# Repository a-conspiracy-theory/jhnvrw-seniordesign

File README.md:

UCF 2026 Senior Design Project

RF Energy Harvesting Ultra-Low-power Transceiver for Environmental Sensing

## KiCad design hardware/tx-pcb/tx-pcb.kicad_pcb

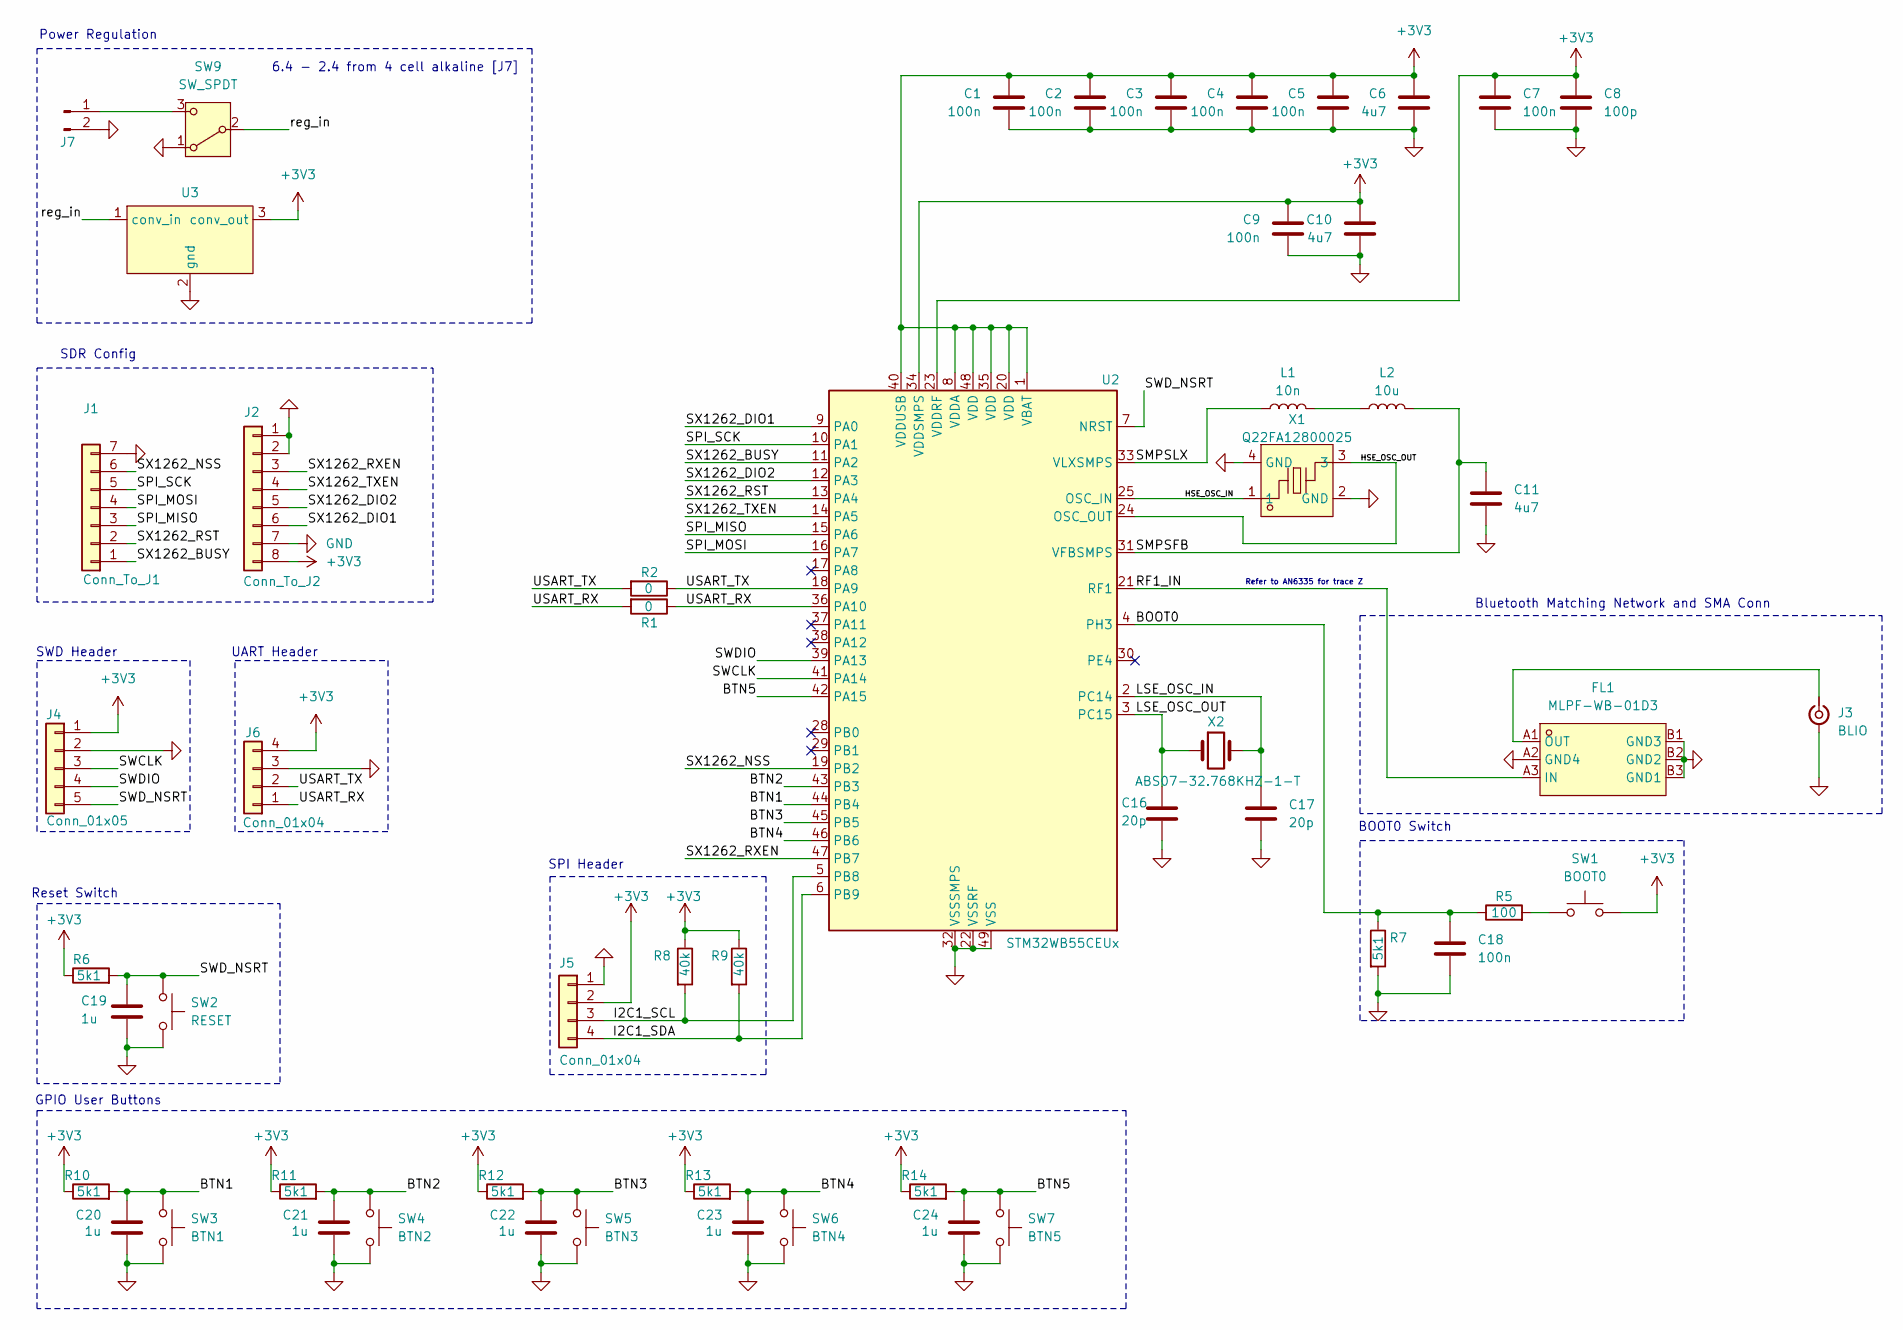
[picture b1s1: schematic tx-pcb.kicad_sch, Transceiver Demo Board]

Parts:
C1, C2, C3, C4, C5, C7, C9, C18: 100n; C_0603_1608Metric_Pad1.08x0.95mm_HandSolder
C6, C10, C11: 4u7; C_0603_1608Metric_Pad1.08x0.95mm_HandSolder
C8: 100p; C_0603_1608Metric_Pad1.08x0.95mm_HandSolder
C16, C17: 20p; C_0603_1608Metric_Pad1.08x0.95mm_HandSolder
C19, C20, C21, C22, C23, C24: 1u; C_0603_1608Metric_Pad1.08x0.95mm_HandSolder
FL1: MLPF-WB-01D3; BGA-6_L1.6-W1.0-R3-C2-P0.50-TL; MPN MLPF-WB-01D3; LCSC Part C5440144
J1: Conn_To_J1; PinHeader_1x07_P2.54mm_Vertical
J2: Conn_To_J2; PinHeader_1x08_P2.54mm_Vertical
J3: BLIO; SMA_Samtec_SMA-J-P-H-ST-EM1_EdgeMount
J4: Conn_01x05; PinHeader_1x05_P2.54mm_Vertical
J5, J6: Conn_01x04; PinHeader_1x04_P2.54mm_Vertical
J7: Conn_01x02_Pin; PinHeader_1x02_P2.54mm_Vertical
L1: 10n; L_0805_2012Metric_Pad1.05x1.20mm_HandSolder
L2: 10u; L_0805_2012Metric_Pad1.05x1.20mm_HandSolder
R1, R2: 0; R_0805_2012Metric_Pad1.20x1.40mm_HandSolder
R5: 100; R_0805_2012Metric_Pad1.20x1.40mm_HandSolder
R6, R7, R10, R11, R12, R13, R14: 5k1; R_0805_2012Metric_Pad1.20x1.40mm_HandSolder
R8, R9: 40k; R_0805_2012Metric_Pad1.20x1.40mm_HandSolder
SW1: BOOT0; SW_PUSH_6mm
SW2: RESET; SW_PUSH_6mm
SW3: BTN1; SW_PUSH_6mm
SW4: BTN2; SW_PUSH_6mm
SW5: BTN3; SW_PUSH_6mm
SW6: BTN4; SW_PUSH_6mm
SW7: BTN5; SW_PUSH_6mm
SW9: SW_SPDT; spdt_amazon
U2: STM32WB55CEUx; QFN-48-1EP_7x7mm_P0.5mm_EP5.6x5.6mm
U3: TPS63070_board
X1: Q22FA12800025; CRYSTAL-SMD_4P-L2.0-W1.6-BL; MPN Q22FA12800025; LCSC Part C187794
X2: ABS07-32.768KHZ-1-T; OSC-SMD_2P-L3.2-W1.5

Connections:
+3V3: C1.1, C2.1, C3.1, C4.1, C5.1, C6.1, C7.1, C8.1, C9.1, C10.1, J2.8, J4.1, J5.2, J6.4, R6.1, R8.1, R9.1, R10.1, R11.1, R12.1, R13.1, R14.1, SW1.2, U2.1 (VBAT), U2.8 (VDDA), U2.20 (VDD), U2.23 (VDDRF), U2.34 (VDDSMPS), U2.35 (VDD), U2.40 (VDDUSB), U2.48 (VDD), U3.3 (conv_out)
/BOOT0: C18.2, R5.1, R7.1, U2.4 (PH3)
/BTN1: C20.1, R10.2, SW3.1, U2.44 (PB4)
/BTN2: C21.1, R11.2, SW4.1, U2.43 (PB3)
/BTN3: C22.1, R12.2, SW5.1, U2.45 (PB5)
/BTN4: C23.1, R13.2, SW6.1, U2.46 (PB6)
/BTN5: C24.1, R14.2, SW7.1, U2.42 (PA15)
/HSE_OSC_IN: U2.25 (OSC_IN), X1.1
/HSE_OSC_OUT: U2.24 (OSC_OUT), X1.3
/I2C1_SCL: J5.3, R8.2, U2.5 (PB8)
/I2C1_SDA: J5.4, R9.2, U2.6 (PB9)
/LSE_OSC_IN: C17.1, U2.2 (PC14), X2.2
/LSE_OSC_OUT: C16.1, U2.3 (PC15), X2.1
/RF1_IN: FL1.A3 (IN), U2.21 (RF1)
/SMPSFB: C11.1, L2.2, U2.31 (VFBSMPS)
/SMPSLX: L1.1, U2.33 (VLXSMPS)
/SPI_MISO: J1.3, U2.15 (PA6)
/SPI_MOSI: J1.4, U2.16 (PA7)
/SPI_SCK: J1.5, U2.10 (PA1)
/SWCLK: J4.3, U2.41 (PA14)
/SWDIO: J4.4, U2.39 (PA13)
/SWD_NSRT: C19.1, J4.5, R6.2, SW2.1, U2.7 (NRST)
/SX1262_BUSY: J1.1, U2.11 (PA2)
/SX1262_DIO1: J2.6, U2.9 (PA0)
/SX1262_DIO2: J2.5, U2.12 (PA3)
/SX1262_NSS: J1.6, U2.19 (PB2)
/SX1262_RST: J1.2, U2.13 (PA4)
/SX1262_RXEN: J2.3, U2.47 (PB7)
/SX1262_TXEN: J2.4, U2.14 (PA5)
/USART_RX: J6.1, R1.1, R1.2, U2.36 (PA10)
/USART_TX: J6.2, R2.1, R2.2, U2.18 (PA9)
/reg_in: SW9.2 (B), U3.1 (conv_in)
GND: C1.2, C2.2, C3.2, C4.2, C5.2, C6.2, C7.2, C8.2, C9.2, C10.2, C11.2, C16.2, C17.2, C18.1, C19.2, C20.2, C21.2, C22.2, C23.2, C24.2, FL1.A2 (GND4), FL1.B1 (GND3), FL1.B2 (GND2), FL1.B3 (GND1), J1.7, J2.1, J2.2, J2.7, J3.2 (Ext), J4.2, J5.1, J6.3, J7.2, R7.2, SW2.2, SW3.2, SW4.2, SW5.2, SW6.2, SW7.2, SW9.1 (A), U2.22 (VSSRF), U2.32 (VSSSMPS), U2.49 (VSS), U3.2 (gnd), X1.2 (GND), X1.4 (GND)
unnamed: FL1.A1 (OUT), J3.1 (In)
unnamed: J7.1, SW9.3 (C)
unnamed: L1.2, L2.1
unnamed: R5.2, SW1.1

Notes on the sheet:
Power Regulation
6.4 - 2.4 from 4 cell alkaline [J7]
SPI Header
SWD Header
SDR Config
Reset Switch
GPIO User Buttons
Bluetooth Matching Network and SMA Conn
BOOT0 Switch
Refer to AN6335 for trace Z
UART Header

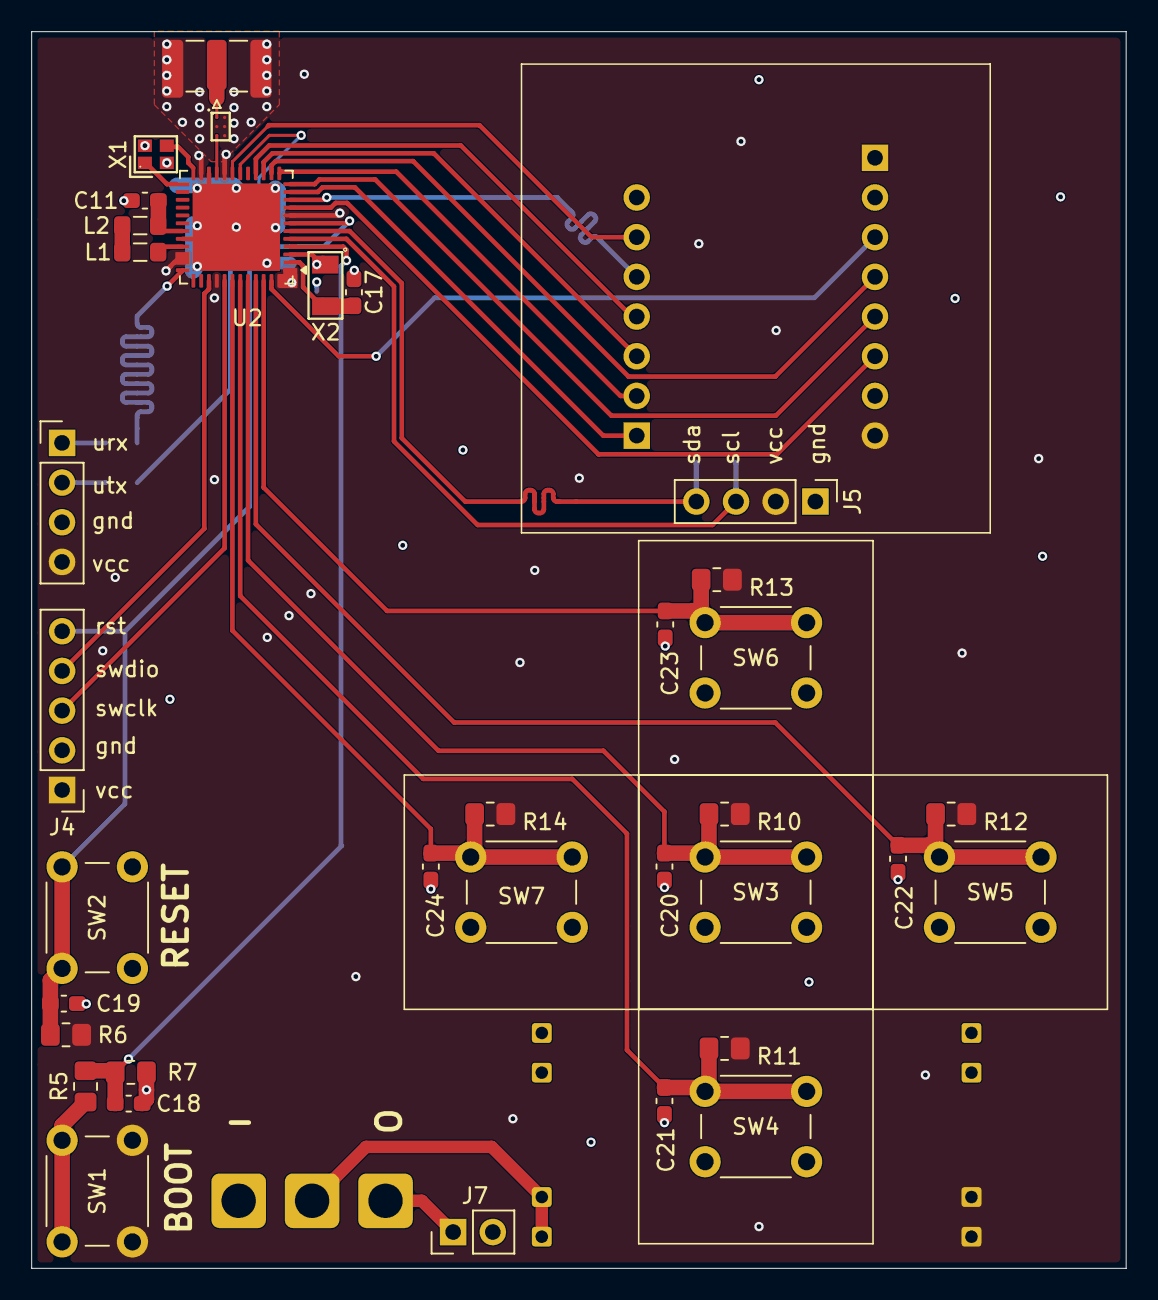
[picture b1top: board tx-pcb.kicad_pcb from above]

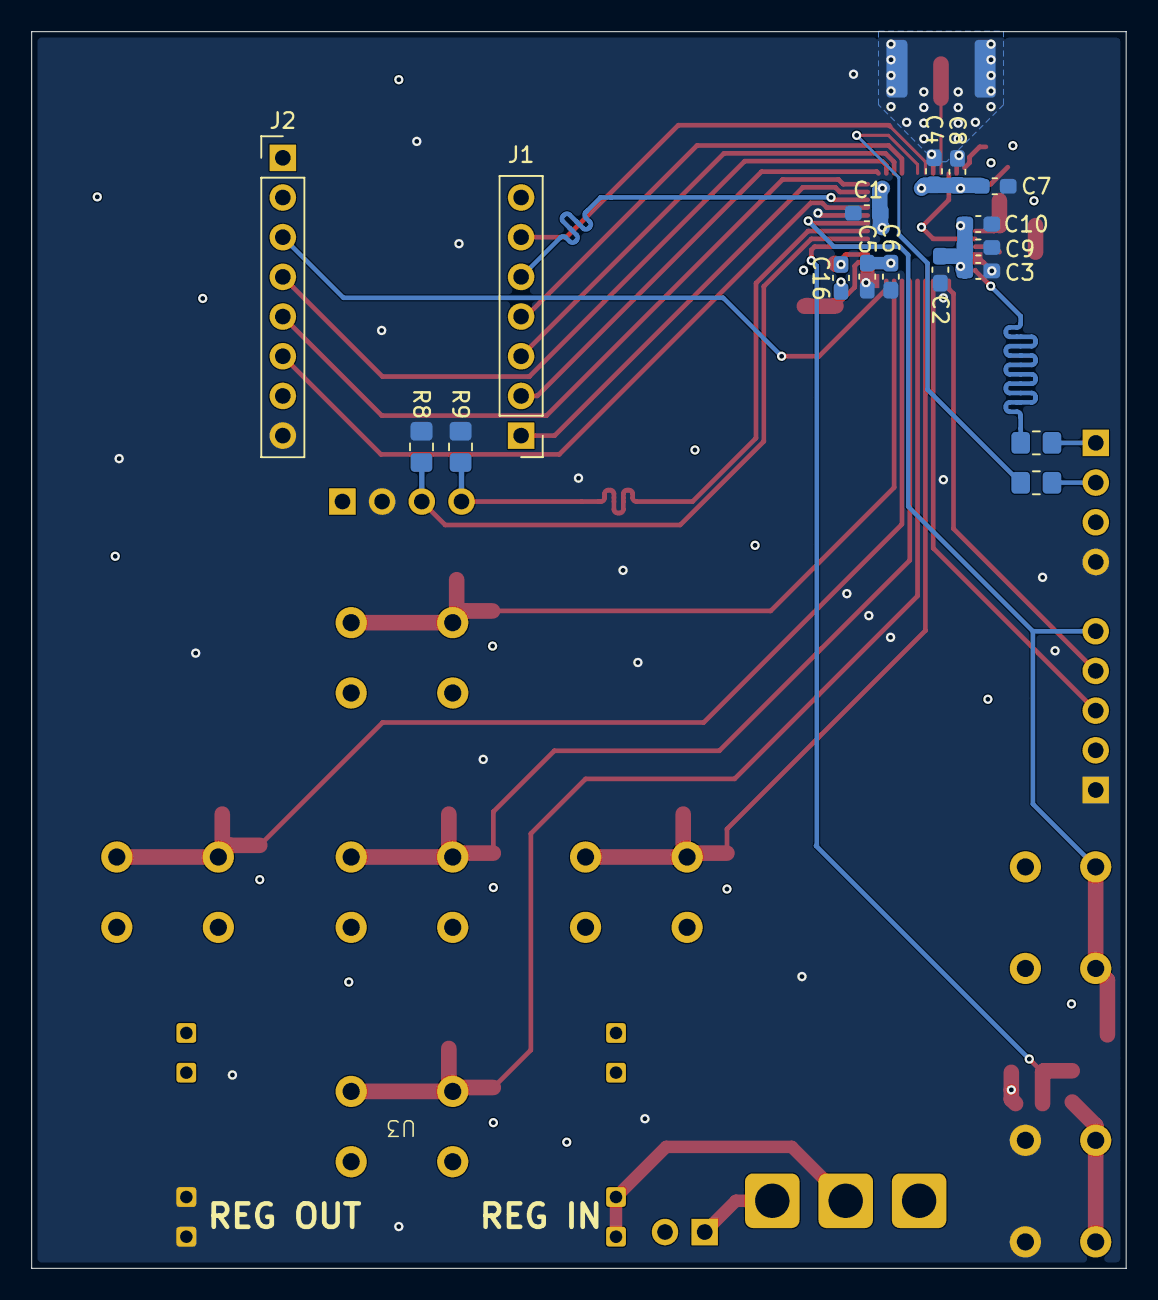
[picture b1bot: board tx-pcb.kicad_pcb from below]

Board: 4 copper layers, 70.0 x 79.1 mm, 54 parts (18 on the bottom side), 37 nets.

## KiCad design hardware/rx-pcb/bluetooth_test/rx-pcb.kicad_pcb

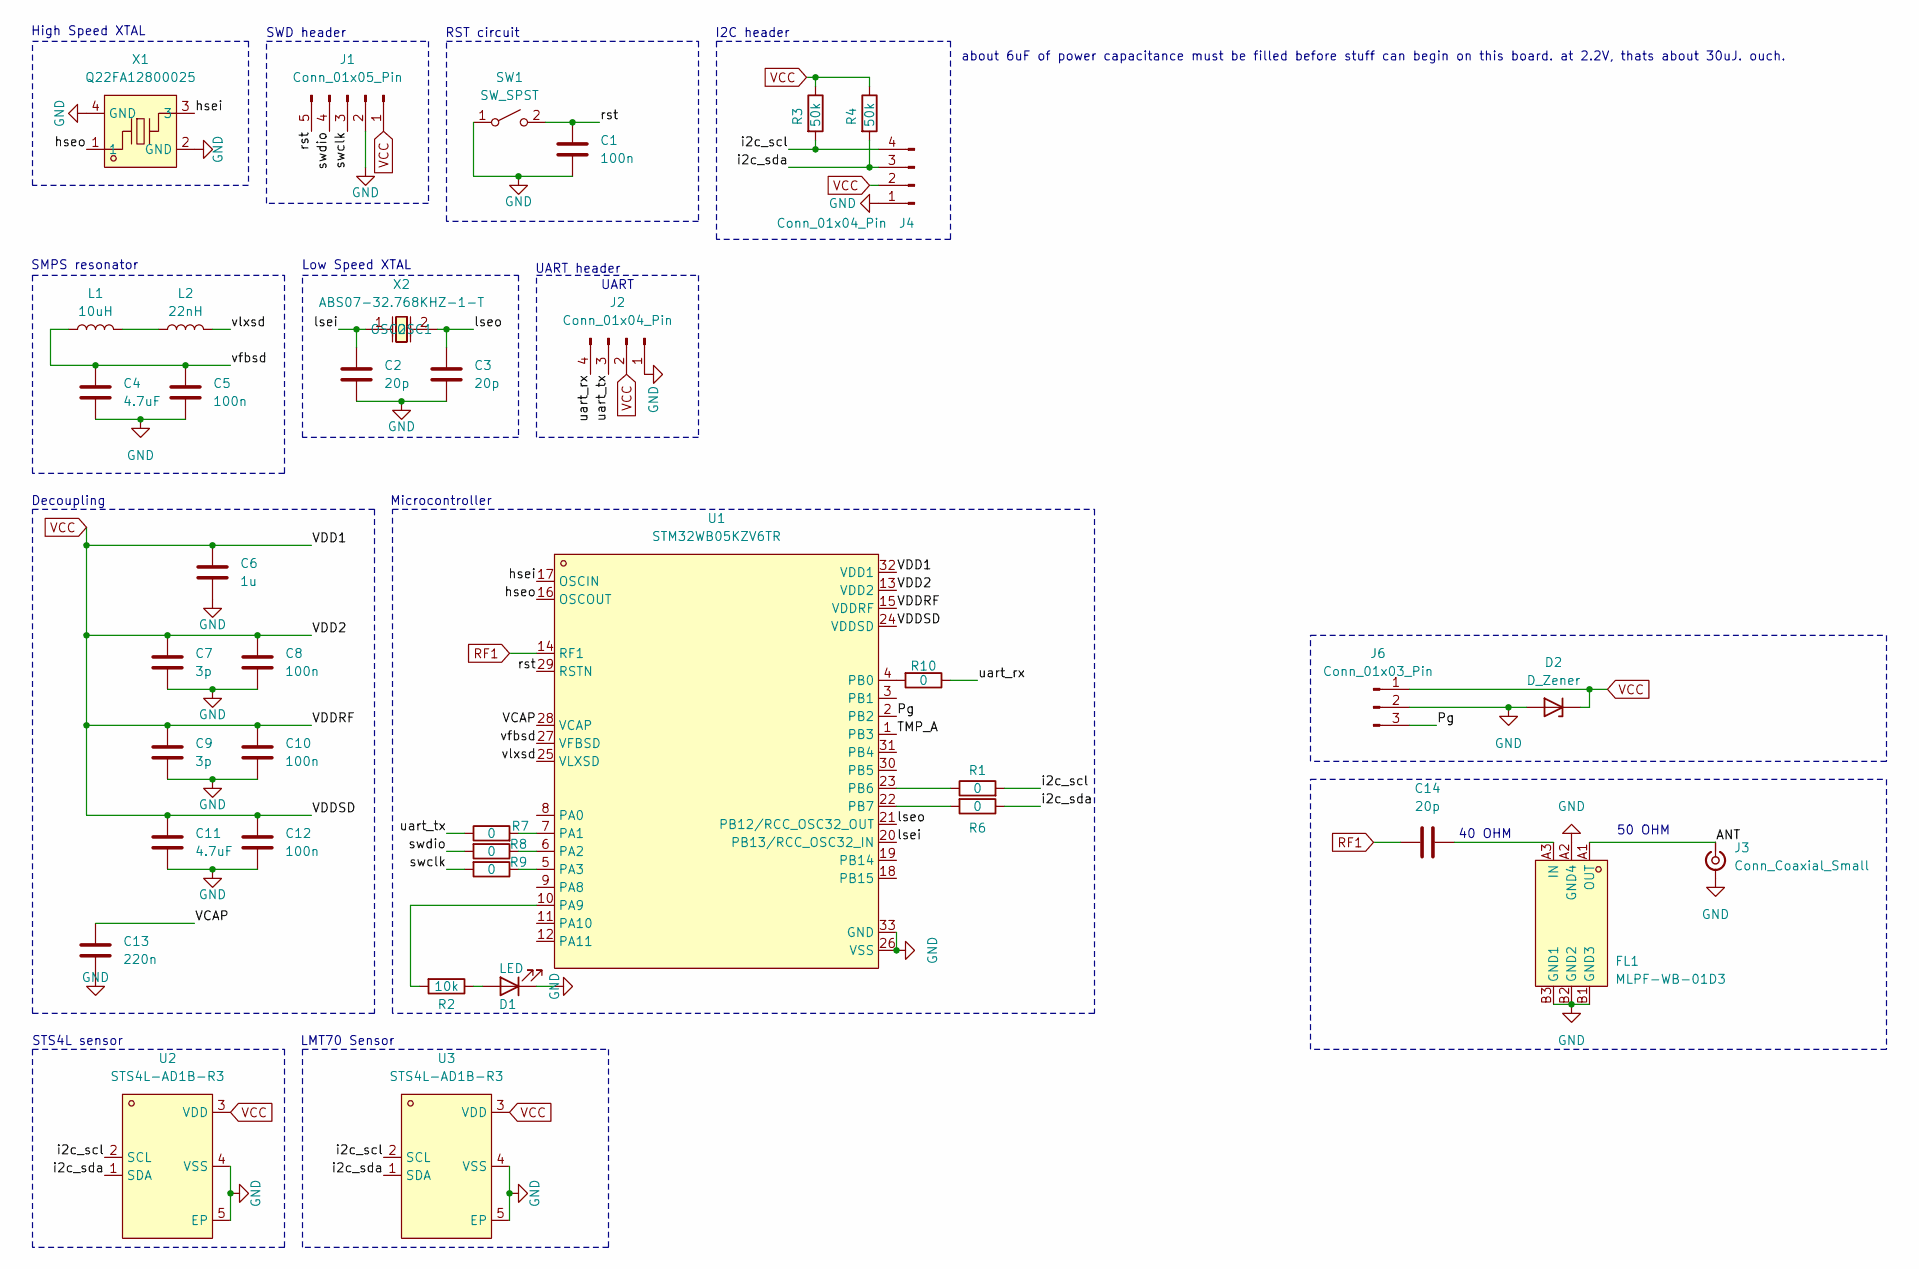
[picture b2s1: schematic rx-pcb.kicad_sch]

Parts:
C1, C5, C8, C10, C12: 100n; C_0805_2012Metric_Pad1.18x1.45mm_HandSolder
C2, C3: 20p; C_0805_2012Metric_Pad1.18x1.45mm_HandSolder
C4, C11: 4.7uF; C_0805_2012Metric_Pad1.18x1.45mm_HandSolder
C6: 1u; C_0805_2012Metric_Pad1.18x1.45mm_HandSolder
C7, C9: 3p; C_0805_2012Metric_Pad1.18x1.45mm_HandSolder
C13: 220n; C_0805_2012Metric_Pad1.18x1.45mm_HandSolder
C14: 20p; R_0201_0603Metric_Pad0.64x0.40mm_HandSolder_correctedcleara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
D1: LED; LED_0805_2012Metric_Pad1.15x1.40mm_HandSolder
D2: D_Zener; D_0603_1608Metric_Pad1.05x0.95mm_HandSolder
FL1: MLPF-WB-01D3; BGA-6_L1.6-W1.0-R3-C2-P0.50-TL; MPN MLPF-WB-01D3; LCSC Part C5440144
J1: Conn_01x05_Pin; PinHeader_1x05_P2.54mm_Vertical
J2, J4: Conn_01x04_Pin; PinHeader_1x04_P2.54mm_Vertical
J3: Conn_Coaxial_Small; SMA_Samtec_SMA-J-P-H-ST-EM1_EdgeMount
J6: Conn_01x03_Pin; PinHeader_1x03_P2.54mm_Vertical
L1: 10uH; L_0805_2012Metric_Pad1.05x1.20mm_HandSolder
L2: 22nH; L_0805_2012Metric_Pad1.05x1.20mm_HandSolder
R1, R6: 0; R_0805_2012Metric_Pad1.20x1.40mm_HandSolder
R2: 10k; R_0805_2012Metric_Pad1.20x1.40mm_HandSolder
R3, R4: 50k; R_0805_2012Metric_Pad1.20x1.40mm_HandSolder
R7, R8, R9, R10: 0; R_0805_2012Metric
SW1: SW_SPST; SW_PUSH_6mm
U1: STM32WB05KZV6TR; UFQFN-32_L5.0-W5.0-P0.50-TL-EP3.5; MPN STM32WB05KZV6TR; LCSC Part C28314403
U2, U3: STS4L-AD1B-R3; DFN-4_L1.5-W1.5-P0.80-TL-EP; MPN STS4L-AD1B-R3; LCSC Part C41410764
X1: Q22FA12800025; CRYSTAL-SMD_4P-L2.0-W1.6-BL; MPN Q22FA12800025; LCSC Part C187794
X2: ABS07-32.768KHZ-1-T; OSC-SMD_2P-L3.2-W1.5; MPN ABS07-32.768KHz-1-T; LCSC Part C145140

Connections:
/ANT: FL1.A1 (OUT), J3.1 (In)
/Pg: J6.3, U1.2 (PB2)
/TMP_A: U1.1 (PB3)
/VCAP: C13.1, U1.28 (VCAP)
/hsei: U1.17 (OSCIN), X1.3
/hseo: U1.16 (OSCOUT), X1.1
/i2c_scl: J4.4, R1.2, R3.2, U2.2 (SCL), U3.2 (SCL)
/i2c_sda: J4.3, R4.2, R6.1, U2.1 (SDA), U3.1 (SDA)
/lsei: C2.1, U1.20 (PB13/RCC_OSC32_IN), X2.1 (OSC1)
/lseo: C3.1, U1.21 (PB12/RCC_OSC32_OUT), X2.2 (OSC2)
/rst: C1.1, J1.5, SW1.2 (B), U1.29 (RSTN)
/swclk: J1.3, R9.2
/swdio: J1.4, R8.2
/uart_rx: J2.4, R10.1
/uart_tx: J2.3, R7.1
/vfbsd: C4.1, C5.1, L1.1, U1.27 (VFBSD)
/vlxsd: L2.2, U1.25 (VLXSD)
GND: C1.2, C2.2, C3.2, C4.2, C5.2, C6.2, C7.2, C8.2, C9.2, C10.2, C11.2, C12.2, C13.2, D1.1 (K), D2.2 (A), FL1.A2 (GND4), FL1.B1 (GND3), FL1.B2 (GND2), FL1.B3 (GND1), J1.2, J2.1, J3.2 (Ext), J4.1, J6.2, SW1.1 (A), U1.26 (VSS), U1.33 (GND), U2.4 (VSS), U2.5 (EP), U3.4 (VSS), U3.5 (EP), X1.2 (GND), X1.4 (GND)
unnamed: D1.2 (A), R2.1
unnamed: C14.2, FL1.A3 (IN)
unnamed: L1.2, L2.1
unnamed: R7.2, U1.7 (PA1)
unnamed: R8.1, U1.6 (PA2)
unnamed: R9.1, U1.5 (PA3)
unnamed: R2.2, U1.10 (PA9)
unnamed: R10.2, U1.4 (PB0)
unnamed: R1.1, U1.23 (PB6)
unnamed: R6.2, U1.22 (PB7)
RF1: C14.1, U1.14 (RF1)
VCC: C6.1, C7.1, C8.1, C9.1, C10.1, C11.1, C12.1, D2.1 (K), J1.1, J2.2, J4.2, J6.1, R3.1, R4.1, U1.13 (VDD2), U1.15 (VDDRF), U1.24 (VDDSD), U1.32 (VDD1), U2.3 (VDD), U3.3 (VDD)

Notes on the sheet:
Low Speed XTAL
about 6uF of power capacitance must be filled before stuff can begin on this board. at 2.2V, thats about 30uJ. ouch.
40 OHM
UART header
LMT70 Sensor
RST circuit
Microcontroller
SWD header
High Speed XTAL
UART
Decoupling
STS4L sensor
I2C header
SMPS resonator
50 OHM

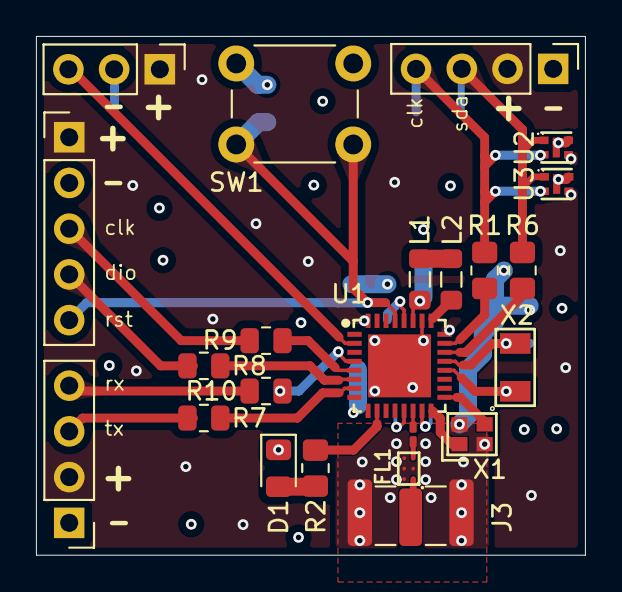
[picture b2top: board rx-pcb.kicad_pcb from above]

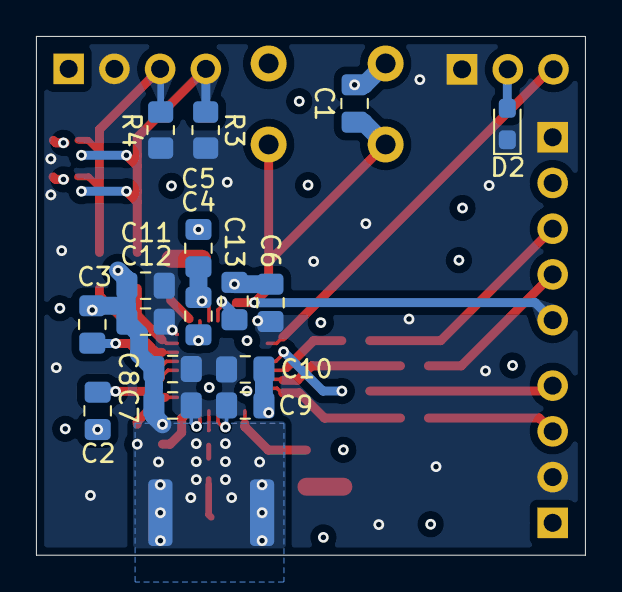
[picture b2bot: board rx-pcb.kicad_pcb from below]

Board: 4 copper layers, 30.5 x 28.8 mm, 39 parts (16 on the bottom side), 29 nets.

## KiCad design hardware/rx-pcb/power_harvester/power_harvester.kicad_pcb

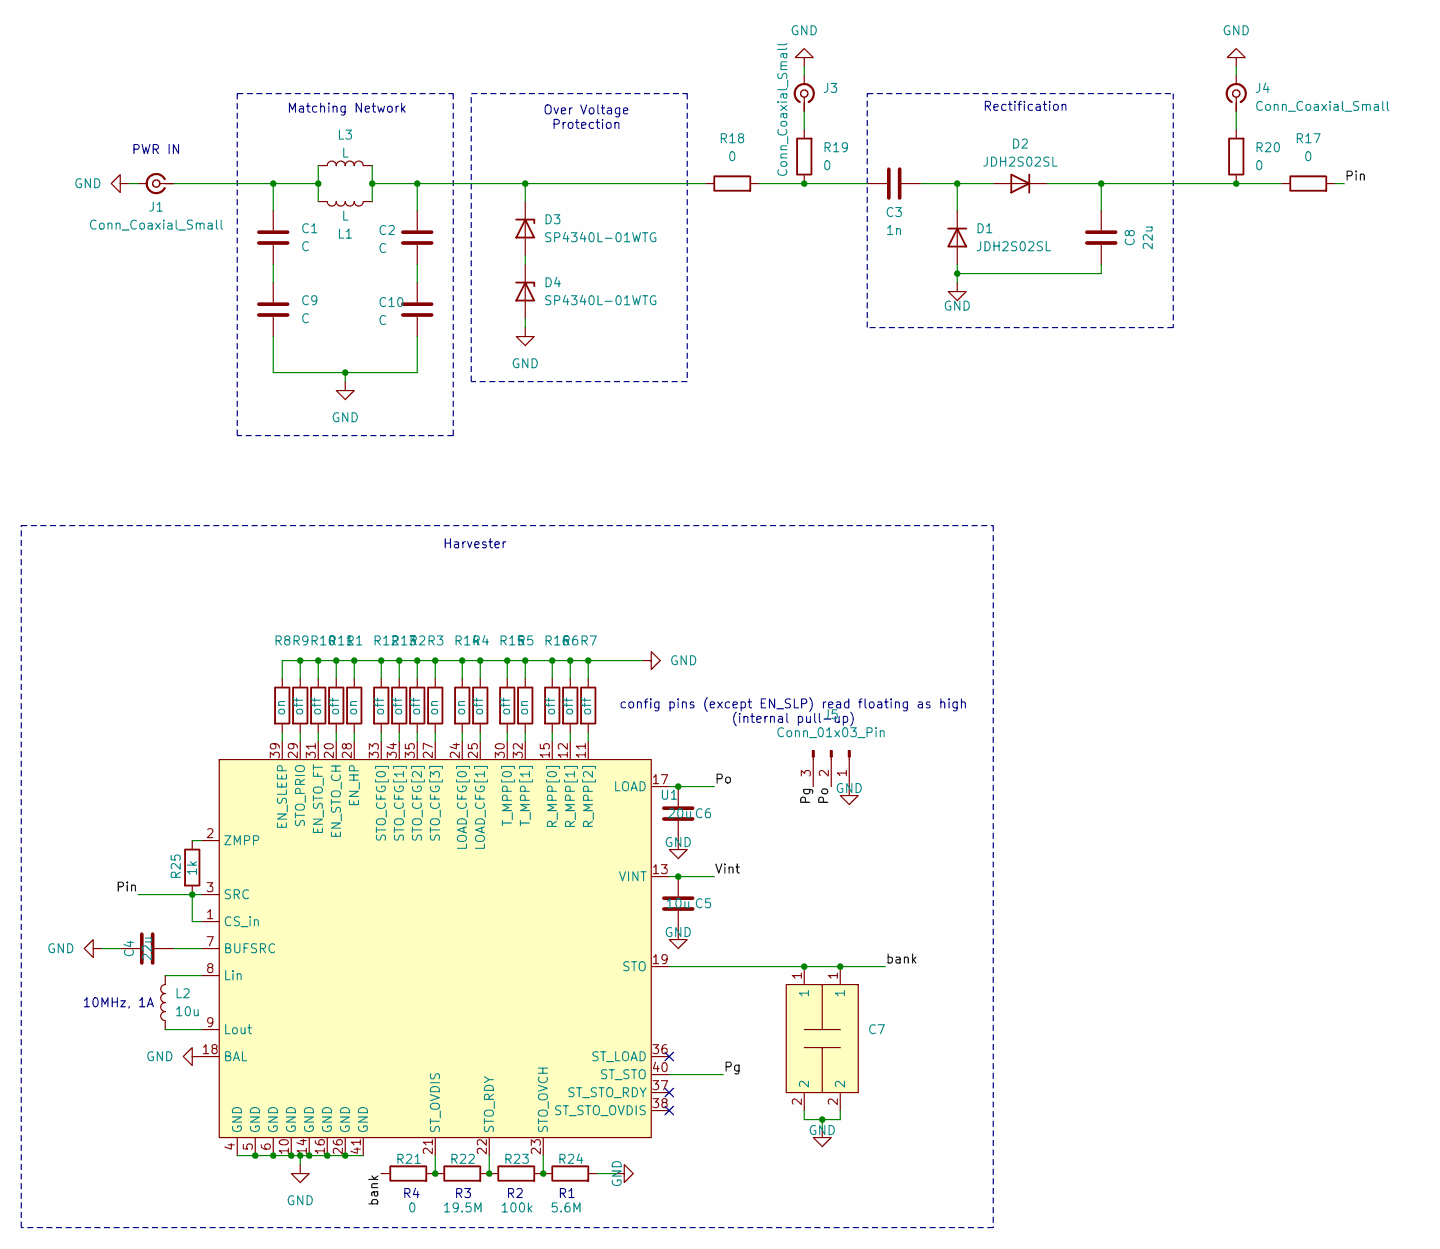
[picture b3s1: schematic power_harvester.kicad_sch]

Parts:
C1, C2, C9, C10: C; C_0402_1005Metric
C3: 1n; C_0402_1005Metric
C4: 22u; C_0603_1608Metric_Pad1.08x0.95mm_HandSolder
C5: 10u; C_0603_1608Metric_Pad1.08x0.95mm_HandSolder
C6: 20u; C_0603_1608Metric_Pad1.08x0.95mm_HandSolder
C7: C4AQXEXXXXXXXAX
C8: 22u; C_0805_2012Metric_Pad1.18x1.45mm_HandSolder
D1, D2: JDH2S02SL; R_0201_0603Metric_correctedclearance
D3, D4: SP4340L-01WTG; R_0201_0603Metric_correctedclearance
J1: Conn_Coaxial_Small; SMA_Amphenol_901-143_Horizontal
J3, J4: Conn_Coaxial_Small; SMA_Molex_73251-2120_EdgeMount_Horizontal
J5: Conn_01x03_Pin; PinHeader_1x03_P2.54mm_Vertical
L1, L3: L; L_0402_1005Metric
L2: 10u; WE-MAPI
R1, R3, R5, R8, R14: on; R_0201_0603Metric_correctedclearance
R2, R4, R6, R7, R9, R10, R11, R12, R13, R15, R16: off; R_0201_0603Metric_correctedclearance
R17, R18, R19, R20: 0; R_0201_0603Metric_correctedclearance
R21: 0; R_0805_2012Metric_Pad1.20x1.40mm_HandSolder
R22: 19.5M; R_0805_2012Metric_Pad1.20x1.40mm_HandSolder
R23: 100k; R_0805_2012Metric_Pad1.20x1.40mm_HandSolder
R24: 5.6M; R_0805_2012Metric_Pad1.20x1.40mm_HandSolder
R25: 1k; R_0805_2012Metric_Pad1.20x1.40mm_HandSolder
U1: QFN-40-1EP_5x5mm_P0.4mm_EP3.8x3.8mm

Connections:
/Pg: J5.3, U1.40 (ST_STO)
/Pin: R17.2, R25.2, U1.1 (CS_in), U1.3 (SRC)
/Po: C6.2, J5.2, U1.17 (LOAD)
/Vint: C5.2, U1.13 (VINT)
/bank: C7.1, R21.1, U1.19 (STO)
GND: C4.1, C5.1, C6.1, C7.2, C8.1, C9.2, C10.2, D1.2 (A), D4.2 (A), J1.2 (Ext), J3.2 (Ext), J4.2 (Ext), J5.1, R1.1, R2.1, R3.1, R4.1, R5.1, R6.1, R7.1, R8.1, R9.1, R10.1, R11.1, R12.1, R13.1, R14.1, R15.1, R16.1, R24.2, U1.4 (GND), U1.5 (GND), U1.6 (GND), U1.10 (GND), U1.14 (GND), U1.16 (GND), U1.18 (BAL), U1.26 (GND), U1.41 (GND)
unnamed: C1.2, C9.1
unnamed: C3.1, R18.2, R19.1
unnamed: C2.2, C10.1
unnamed: C3.2, D1.1 (K), D2.2 (A)
unnamed: C8.2, D2.1 (K), R17.1, R20.1
unnamed: D3.2 (A), D4.1 (K)
unnamed: C2.1, D3.1 (K), L1.1, L3.2, R18.1
unnamed: C1.1, J1.1 (In), L1.2, L3.1
unnamed: J3.1 (In), R19.2
unnamed: J4.1 (In), R20.2
unnamed: C4.2, U1.7 (BUFSRC)
unnamed: R1.2, U1.28 (EN_HP)
unnamed: R8.2, U1.39 (EN_SLEEP)
unnamed: R11.2, U1.20 (EN_STO_CH)
unnamed: R10.2, U1.31 (EN_STO_FT)
unnamed: R14.2, U1.24 (LOAD_CFG[0])
unnamed: R4.2, U1.25 (LOAD_CFG[1])
unnamed: L2.2, U1.8 (Lin)
unnamed: L2.1, U1.9 (Lout)
unnamed: R16.2, U1.15 (R_MPP[0])
unnamed: R6.2, U1.12 (R_MPP[1])
unnamed: R7.2, U1.11 (R_MPP[2])
unnamed: R12.2, U1.33 (STO_CFG[0])
unnamed: R13.2, U1.34 (STO_CFG[1])
unnamed: R2.2, U1.35 (STO_CFG[2])
unnamed: R3.2, U1.27 (STO_CFG[3])
unnamed: R23.2, R24.1, U1.23 (STO_OVCH)
unnamed: R9.2, U1.29 (STO_PRIO)
unnamed: R22.2, R23.1, U1.22 (STO_RDY)
unnamed: R21.2, R22.1, U1.21 (ST_OVDIS)
unnamed: R15.2, U1.30 (T_MPP[0])
unnamed: R5.2, U1.32 (T_MPP[1])
unnamed: R25.1, U1.2 (ZMPP)

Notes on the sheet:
Over Voltage Protection
R4 R3 R2 R1
config pins (except EN_SLP) read floating as high (internal pull-up)
Matching Network
Harvester
Rectification
PWR IN
10MHz, 1A

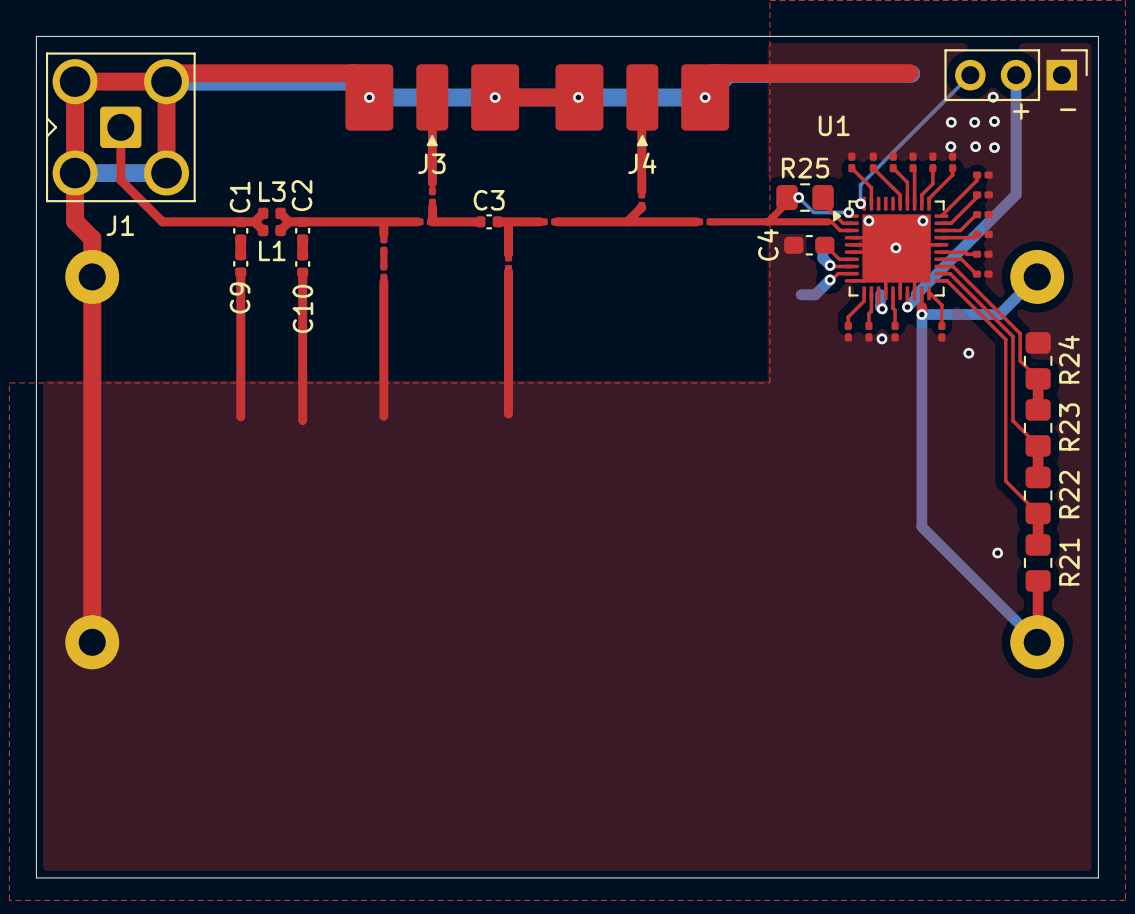
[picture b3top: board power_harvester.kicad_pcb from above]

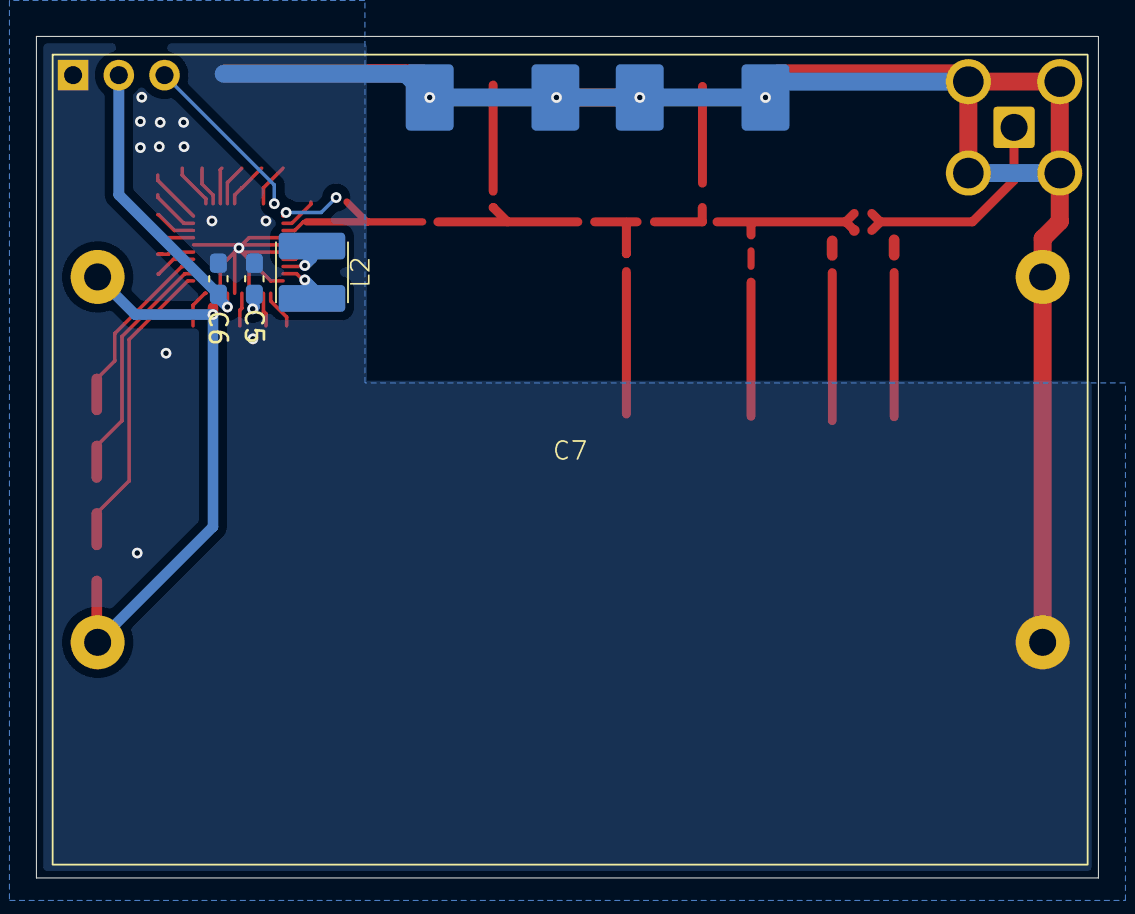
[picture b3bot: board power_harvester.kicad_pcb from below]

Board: 2 copper layers, 59.0 x 46.8 mm, 46 parts (4 on the bottom side), 39 nets.

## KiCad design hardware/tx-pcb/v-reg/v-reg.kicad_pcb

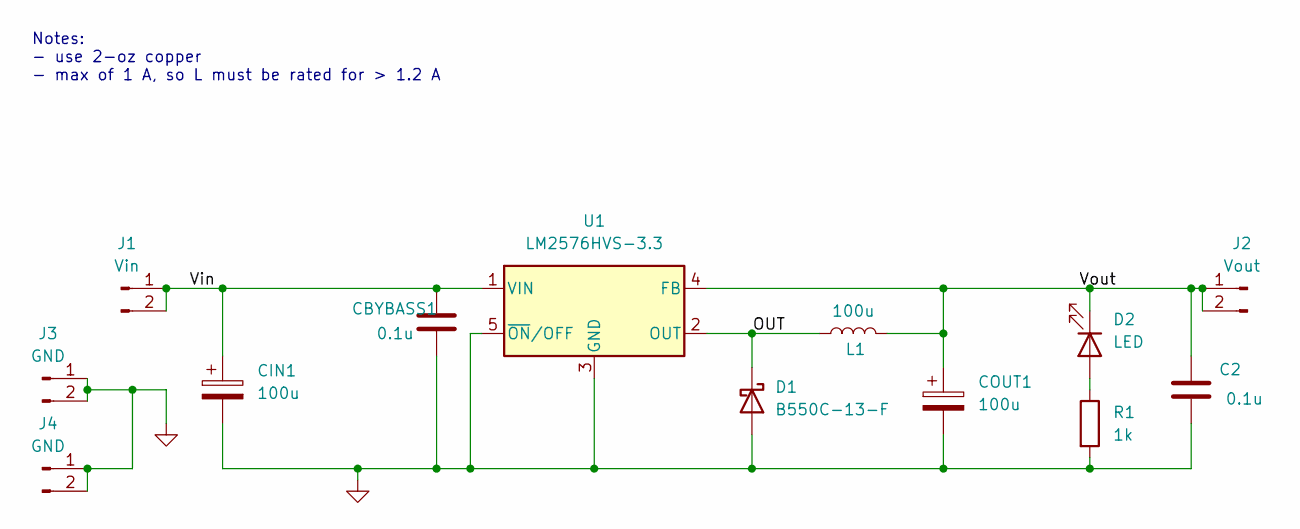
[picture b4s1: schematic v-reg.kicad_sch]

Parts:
C2: 0.1u; C_0805_2012Metric_Pad1.18x1.45mm_HandSolder
CBYBASS1: 0.1u; C_0805_2012Metric_Pad1.18x1.45mm_HandSolder
CIN1: 100u; CP_Radial_D8.0mm_P3.50mm
COUT1: 100u; CP_Radial_D8.0mm_P3.50mm
D1: B550C-13-F; SMC_L6.9-W5.9-LS7.9-RD
D2: LED; LED_0805_2012Metric_Pad1.15x1.40mm_HandSolder
J1: Vin; PinHeader_1x02_P2.54mm_Vertical
J2: Vout; PinHeader_1x02_P2.54mm_Vertical
J3, J4: GND; PinHeader_1x02_P2.54mm_Vertical
L1: 100u; L_Bourns_SRR1260
R1: 1k; R_0805_2012Metric_Pad1.20x1.40mm_HandSolder
U1: LM2576HVS-3.3; TO-263-5_TabPin3

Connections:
/SW: D1.1 (K), L1.1, U1.2 (OUT)
/Vin: CBYBASS1.1, CIN1.1, J1.1, J1.2, U1.1 (VIN)
/Vout: C2.1, COUT1.1, D2.1 (K), J2.1, J2.2, L1.2, U1.4 (FB); also elsewhere on the board
GND: C2.2, CBYBASS1.2, CIN1.2, COUT1.2, D1.2 (A), J3.1, J3.2, J4.1, J4.2, R1.2, U1.3 (GND), U1.5 (~ON/OFF); also elsewhere on the board
unnamed: D2.2 (A), R1.1

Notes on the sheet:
Notes: - use 2-oz copper - max of 1 A, so L must be rated for > 1.2 A

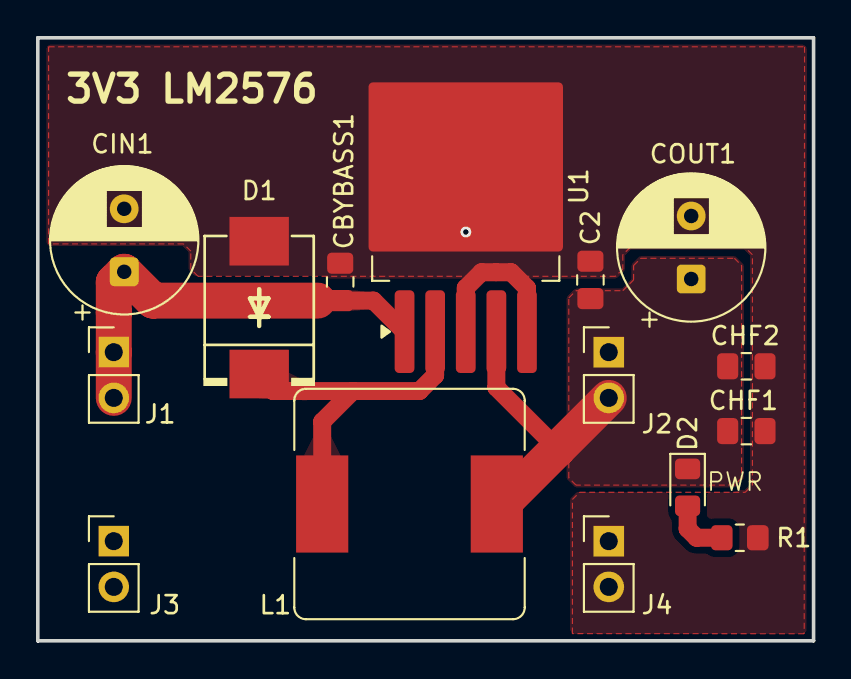
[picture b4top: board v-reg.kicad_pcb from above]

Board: 2 copper layers, 43.1 x 33.5 mm, 15 parts (0 on the bottom side), 5 nets.

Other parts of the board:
CHF1, CHF2: 0.1u; C_0805_2012Metric_Pad1.18x1.45mm_HandSolder

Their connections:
/Vout: CHF1.1, CHF2.1; also elsewhere on the board
GND: CHF1.2, CHF2.2; also elsewhere on the board

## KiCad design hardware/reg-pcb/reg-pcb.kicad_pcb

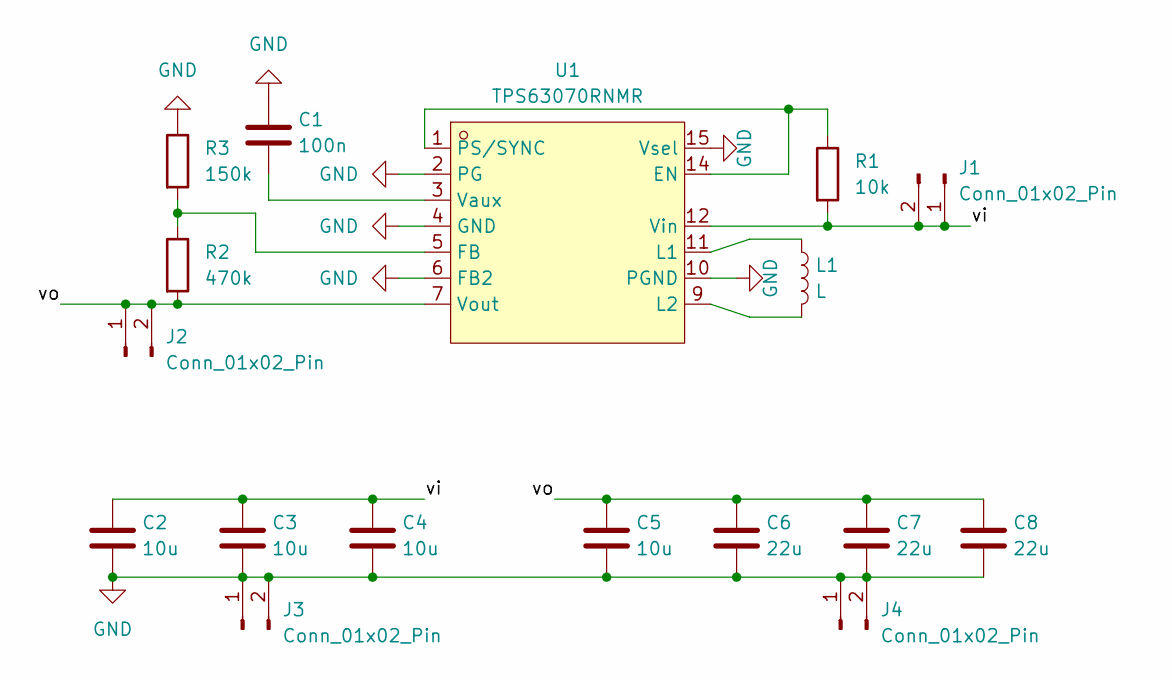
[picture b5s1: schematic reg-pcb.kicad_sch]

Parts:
C1: 100n; C_0805_2012Metric
C2, C3: 10u; C_0805_2012Metric_Pad1.18x1.45mm_HandSolder
C4, C5: 10u; C_0603_1608Metric_Pad1.08x0.95mm_HandSolder
C6, C7, C8: 22u; C_0805_2012Metric_Pad1.18x1.45mm_HandSolder
J1, J2, J3, J4: Conn_01x02_Pin; PinHeader_1x02_P2.54mm_Vertical
L1: L; L_Vishay_IHLP-1616
R1: 10k; R_0805_2012Metric
R2: 470k; R_0805_2012Metric
R3: 150k; R_0805_2012Metric
U1: TPS63070RNMR; VQFN-15_L3.0-W2.5-P0.50-BL; MPN TPS63070RNMR; LCSC Part C109322

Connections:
/vi: C2.1, C3.1, C4.1, J1.1, J1.2, R1.2, U1.12 (Vin)
/vo: C5.1, C6.1, C7.1, C8.1, J2.1, J2.2, R2.2, U1.7 (Vout)
GND: C1.1, C2.2, C3.2, C4.2, C5.2, C6.2, C7.2, C8.2, J3.1, J3.2, J4.1, J4.2, R3.1, U1.2 (PG), U1.4 (GND), U1.6 (FB2), U1.10 (PGND), U1.15 (Vsel)
unnamed: R1.1, U1.1 (PS/SYNC), U1.14 (EN)
unnamed: R2.1, R3.2, U1.5 (FB)
unnamed: L1.1, U1.11 (L1)
unnamed: L1.2, U1.9 (L2)
unnamed: C1.2, U1.3 (Vaux)

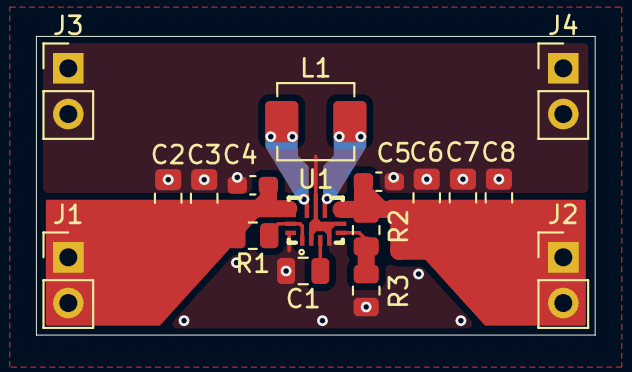
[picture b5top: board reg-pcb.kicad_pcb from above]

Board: 2 copper layers, 31.0 x 16.6 mm, 17 parts (0 on the bottom side), 8 nets.

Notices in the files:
software/WB55/BLE_p2pClient/Core/Src/main.c:
Copyright (c) 2019-2021 STMicroelectronics.
All rights reserved.
This software is licensed under terms that can be found in the LICENSE file
